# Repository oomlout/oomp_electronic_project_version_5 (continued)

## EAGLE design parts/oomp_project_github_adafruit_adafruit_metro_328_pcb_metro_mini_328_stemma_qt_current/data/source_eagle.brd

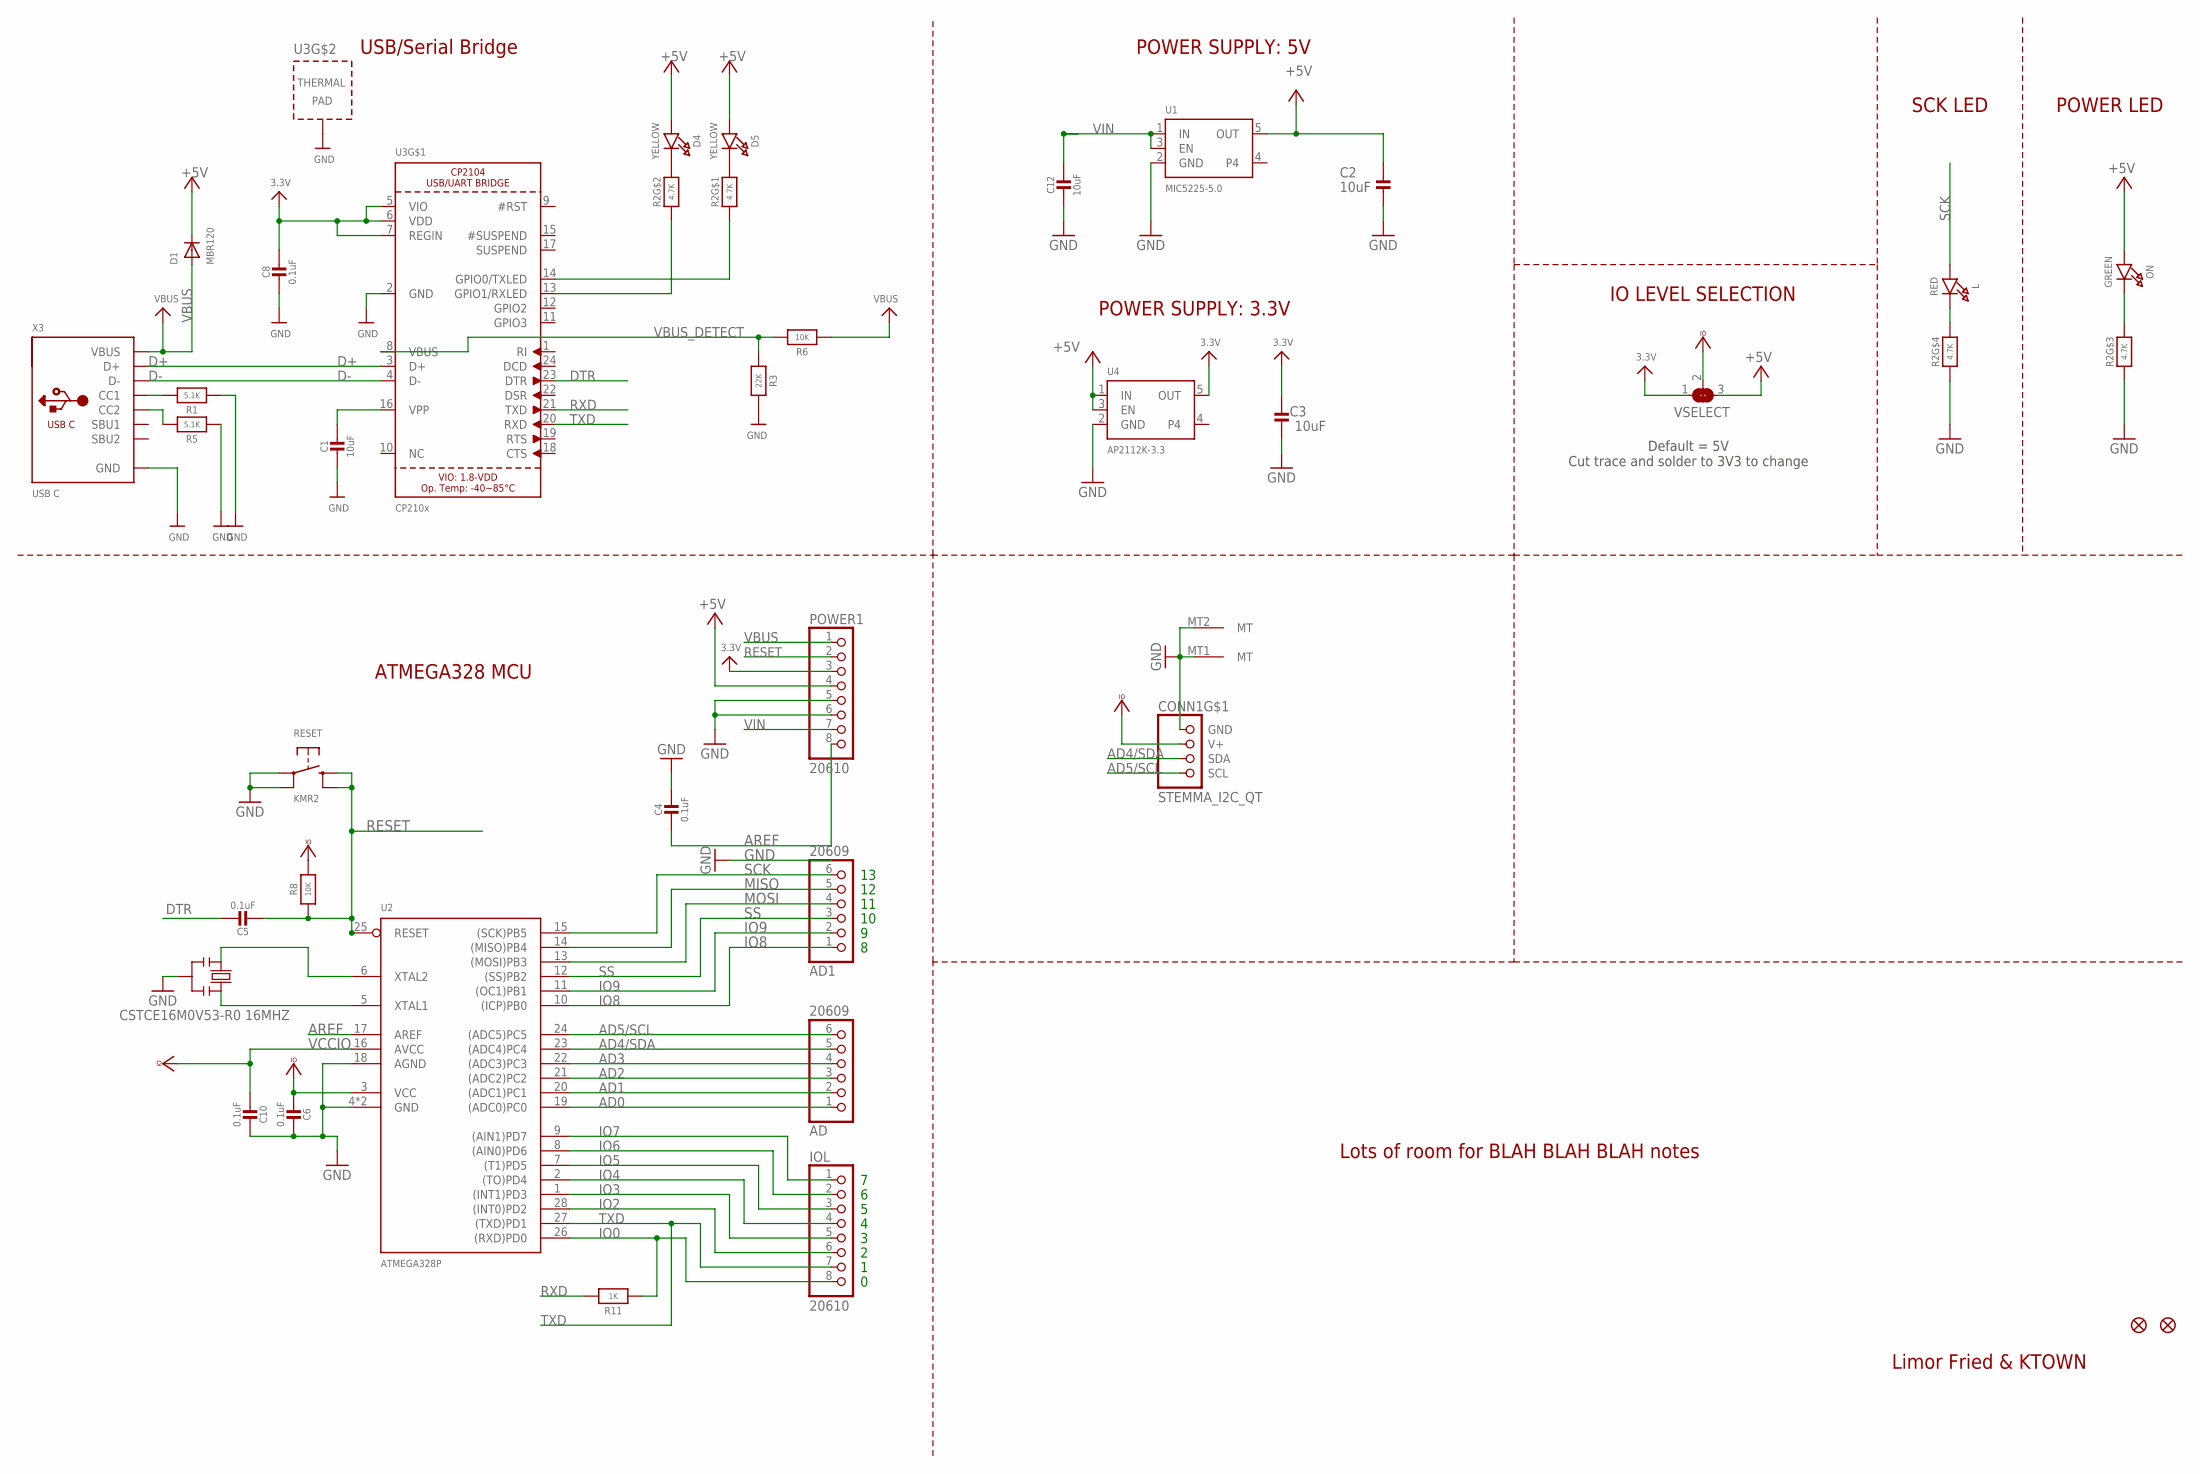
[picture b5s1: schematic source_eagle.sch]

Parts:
AD, AD1: 20609; 1X06_ROUND
C1, C2, C3, C12: 10uF; 0805-NO
C4, C5, C6, C8, C10: 0.1uF; 0603-NO
CONN1: STEMMA_I2C_QT; JST_SH4
D1: MBR120; SOD-123FL
D4, D5: YELLOW; CHIPLED_0603_NOOUTLINE
FD1, FD2: FIDUCIAL_1MM
IOL: 20610; 1X08_ROUND
L: RED; CHIPLED_0603_NOOUTLINE
ON: GREEN; CHIPLED_0603_NOOUTLINE
POWER1: 20610; 1X08_ROUND_70
R1, R5: 5.1K; 0603-NO
R2: 4.7K; RESPACK_4X0603
R3: 22K; 0603-NO
R6, R8: 10K; 0603-NO
R11: 1K; 0603-NO
RESET: KMR2; BTN_KMR2_4.6X2.8
U1: MIC5225-5.0; SOT23-5
U2: ATMEGA328P; QFN28_4MM_.45MM
U3: CP210x; QFN24_4MM_SMSC
U4: AP2112K-3.3; SOT23-5
VSELECT: SOLDERJUMPER_2WAY; SOLDERJUMPER_2WAY_OPEN_NOPASTE
X3: USB C; USB_C_CUSB31-CFM2AX-01-X
Y2: CSTCE16M0V53-R0 16MHZ; RESONATOR

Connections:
3.3V: C3.2, C8.1, POWER1.3, U3.5 (VIO), U3.6 (VDD), U3.7 (REGIN), U4.5 (OUT), VSELECT.1
+5V: C2.2, D1.C, D4.A, D5.A, ON.A, POWER1.4, U1.5 (OUT), U4.1 (IN), U4.3 (EN), VSELECT.3
AD0: AD.1, U2.19 ((ADC0)PC0)
AD1: AD.2, U2.20 ((ADC1)PC1)
AD2: AD.3, U2.21 ((ADC2)PC2)
AD3: AD.4, U2.22 ((ADC3)PC3)
AD4/SDA: AD.5, CONN1.3 (SDA), U2.23 ((ADC4)PC4)
AD5/SCL: AD.6, CONN1.4 (SCL), U2.24 ((ADC5)PC5)
AREF: C4.2, POWER1.8, U2.17 (AREF)
D+: U3.3 (D+), X3.A6 (D+), X3.B6 (D+)
D-: U3.4 (D-), X3.A7 (D-), X3.B7 (D-)
DTR: C5.1, U3.23 (DTR)
GND: C1.2, C2.1, C3.1, C4.1, C6.1, C8.2, C10.1, C12.2, CONN1.1 (GND), CONN1.MT1 (MT), CONN1.MT2 (MT), POWER1.5, POWER1.6, R1.1, R2.3 (1), R2.4 (1), R3.1, R5.1, RESET.A, RESET.A' (P1), U1.2 (GND), U2.4 (GND), U2.18 (AGND), U2.29 (GND), U3.2 (GND), U3.THERM (TP), U4.2 (GND), X3.A1B12 (GND), X3.B1A12 (GND), Y2.2
IO0: IOL.8, R11.1, U2.26 ((RXD)PD0)
IO2: IOL.6, U2.28 ((INT0)PD2)
IO3: IOL.5, U2.1 ((INT1)PD3)
IO4: IOL.4, U2.2 ((TO)PD4)
IO5: IOL.3, U2.7 ((T1)PD5)
IO6: IOL.2, U2.8 ((AIN0)PD6)
IO7: IOL.1, U2.9 ((AIN1)PD7)
IO8: AD1.1, U2.10 ((ICP)PB0)
IO9: AD1.2, U2.11 ((OC1)PB1)
MISO: AD1.5, U2.14 ((MISO)PB4)
MOSI: AD1.4, U2.13 ((MOSI)PB3)
unnamed: L.C, R2.5 (2)
unnamed: ON.C, R2.6 (2)
unnamed: R2.1, U3.14 (GPIO0/TXLED)
unnamed: R1.2, X3.A5 (CC1)
unnamed: D4.C, R2.7 (2)
unnamed: D5.C, R2.8 (2)
unnamed: R5.2, X3.B5 (CC2)
unnamed: C1.1, U3.16 (VPP)
unnamed: R2.2 (1), U3.13 (GPIO1/RXLED)
RESET: C5.2, POWER1.2, R8.1, RESET.B (S), RESET.B' (S1), U2.25 (RESET)
RXD: R11.2, U3.21 (TXD)
SCK: AD1.6, L.A, U2.15 ((SCK)PB5)
SS: AD1.3, U2.12 ((SS)PB2)
TXD: IOL.7, U2.27 ((TXD)PD1), U3.20 (RXD)
VBUS: D1.A, POWER1.1, R6.2, X3.A4B9 (VBUS), X3.B4A9 (VBUS)
VBUS_DETECT: R3.2, R6.1, U3.8 (VBUS)
VCCIO: C6.2, C10.2, CONN1.2 (V+), R8.2, U2.3 (VCC), U2.16 (AVCC), VSELECT.2
VIN: C12.1, POWER1.7, U1.1 (IN), U1.3 (EN)
XTAL1: U2.5 (XTAL1), Y2.3
XTAL2: U2.6 (XTAL2), Y2.1

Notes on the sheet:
Limor Fried & KTOWN
POWER SUPPLY: 5V
USB/Serial Bridge
POWER SUPPLY: 3.3V
IO LEVEL SELECTION
POWER LED
ATMEGA328 MCU
SCK LED
Lots of room for BLAH BLAH BLAH notes
Default = 5V Cut trace and solder to 3V3 to change

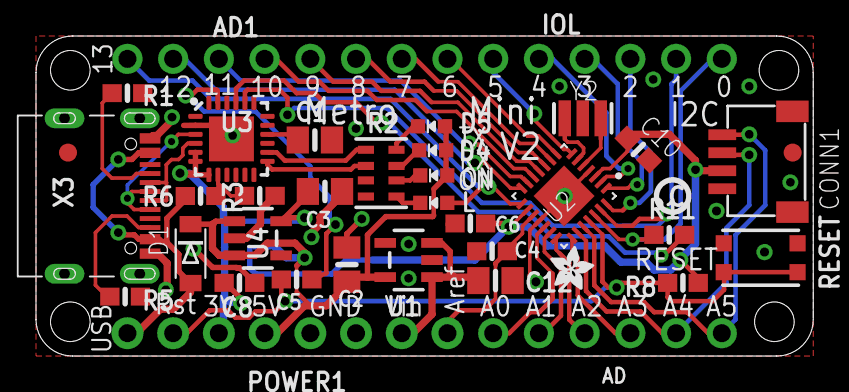
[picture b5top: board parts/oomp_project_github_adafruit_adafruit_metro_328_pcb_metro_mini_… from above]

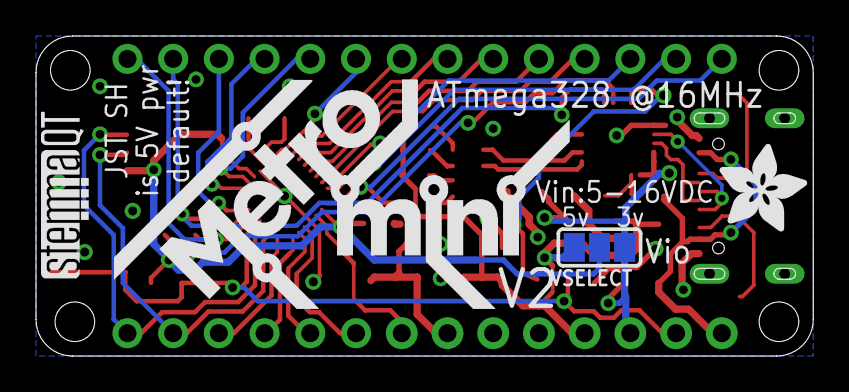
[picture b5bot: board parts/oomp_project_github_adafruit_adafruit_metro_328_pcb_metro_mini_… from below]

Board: 2 copper layers, 43.2 x 17.8 mm, 41 parts (4 on the bottom side), 44 nets.

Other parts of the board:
U$4: PCBFEAT-REV-040
U$5: ADAFRUIT_2.5MM
U$6: STEMMAQT
U$7: METROMINI_SILK
U$10: ADAFRUIT_5MM

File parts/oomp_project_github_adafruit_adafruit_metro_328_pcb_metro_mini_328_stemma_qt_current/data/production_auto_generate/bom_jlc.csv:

Comment,Designator,Footprint,LCSC Part #
,U$5,Metro Mini 328 V2 - STEMMA QT-import-fps:ADAFRUIT_2.5MM,
,U$10,Metro Mini 328 V2 - STEMMA QT-import-fps:ADAFRUIT_5MM,
,U$7,Metro Mini 328 V2 - STEMMA QT-import-fps:METROMINI_SILK,
,U$4,Metro Mini 328 V2 - STEMMA QT-import-fps:PCBFEAT-REV-040,
,VSELECT0,Metro Mini 328 V2 - STEMMA QT-import-fps:SOLDERJUMPER_2WAY_OPEN_NOPASTE,
,U$6,Metro Mini 328 V2 - STEMMA QT-import-fps:STEMMAQT,
0.1uF,"C4,C5,C6,C8,C10",Metro Mini 328 V2 - STEMMA QT-import-fps:0603-NO,C14663
10K,"R6,R8",Metro Mini 328 V2 - STEMMA QT-import-fps:0603-NO,C98220
10uF,"C1,C2,C3,C12",Metro Mini 328 V2 - STEMMA QT-import-fps:0805-NO,
1K,R11,Metro Mini 328 V2 - STEMMA QT-import-fps:0603-NO,C2907002
20609,"AD0,AD1",Metro Mini 328 V2 - STEMMA QT-import-fps:1X06_ROUND,C37208
20610,IOL0,Metro Mini 328 V2 - STEMMA QT-import-fps:1X08_ROUND,C492421
20610,POWER1,Metro Mini 328 V2 - STEMMA QT-import-fps:1X08_ROUND_70,C492421
22K,R3,Metro Mini 328 V2 - STEMMA QT-import-fps:0603-NO,C31850
4.7K,R2,Metro Mini 328 V2 - STEMMA QT-import-fps:RESPACK_4X0603,C23162
5.1K,"R1,R5",Metro Mini 328 V2 - STEMMA QT-import-fps:0603-NO,C23186
AP2112K-3.3,U4,Metro Mini 328 V2 - STEMMA QT-import-fps:SOT23-5,
ATMEGA328P,U2,Metro Mini 328 V2 - STEMMA QT-import-fps:QFN28_4MM_.45MM,
CP210x,U3,Metro Mini 328 V2 - STEMMA QT-import-fps:QFN24_4MM_SMSC,
CSTCE16M0V53-R0 16MHZ,Y2,Metro Mini 328 V2 - STEMMA QT-import-fps:RESONATOR,
FIDUCIAL_1MM,"FD1,FD2",Metro Mini 328 V2 - STEMMA QT-import-fps:FIDUCIAL_1MM,
GREEN,ON0,Metro Mini 328 V2 - STEMMA QT-import-fps:CHIPLED_0603_NOOUTLINE,
KMR2,RESET0,Metro Mini 328 V2 - STEMMA QT-import-fps:BTN_KMR2_4.6X2.8,
MBR120,D1,Metro Mini 328 V2 - STEMMA QT-import-fps:SOD-123FL,
MIC5225-5.0,U1,Metro Mini 328 V2 - STEMMA QT-import-fps:SOT23-5,
RED,L0,Metro Mini 328 V2 - STEMMA QT-import-fps:CHIPLED_0603_NOOUTLINE,
STEMMA_I2C_QT,CONN1,Metro Mini 328 V2 - STEMMA QT-import-fps:JST_SH4,C160404
USB C,X3,Metro Mini 328 V2 - STEMMA QT-import-fps:USB_C_CUSB31-CFM2AX-01-X,
YELLOW,"D4,D5",Metro Mini 328 V2 - STEMMA QT-import-fps:CHIPLED_0603_NOOUTLINE,

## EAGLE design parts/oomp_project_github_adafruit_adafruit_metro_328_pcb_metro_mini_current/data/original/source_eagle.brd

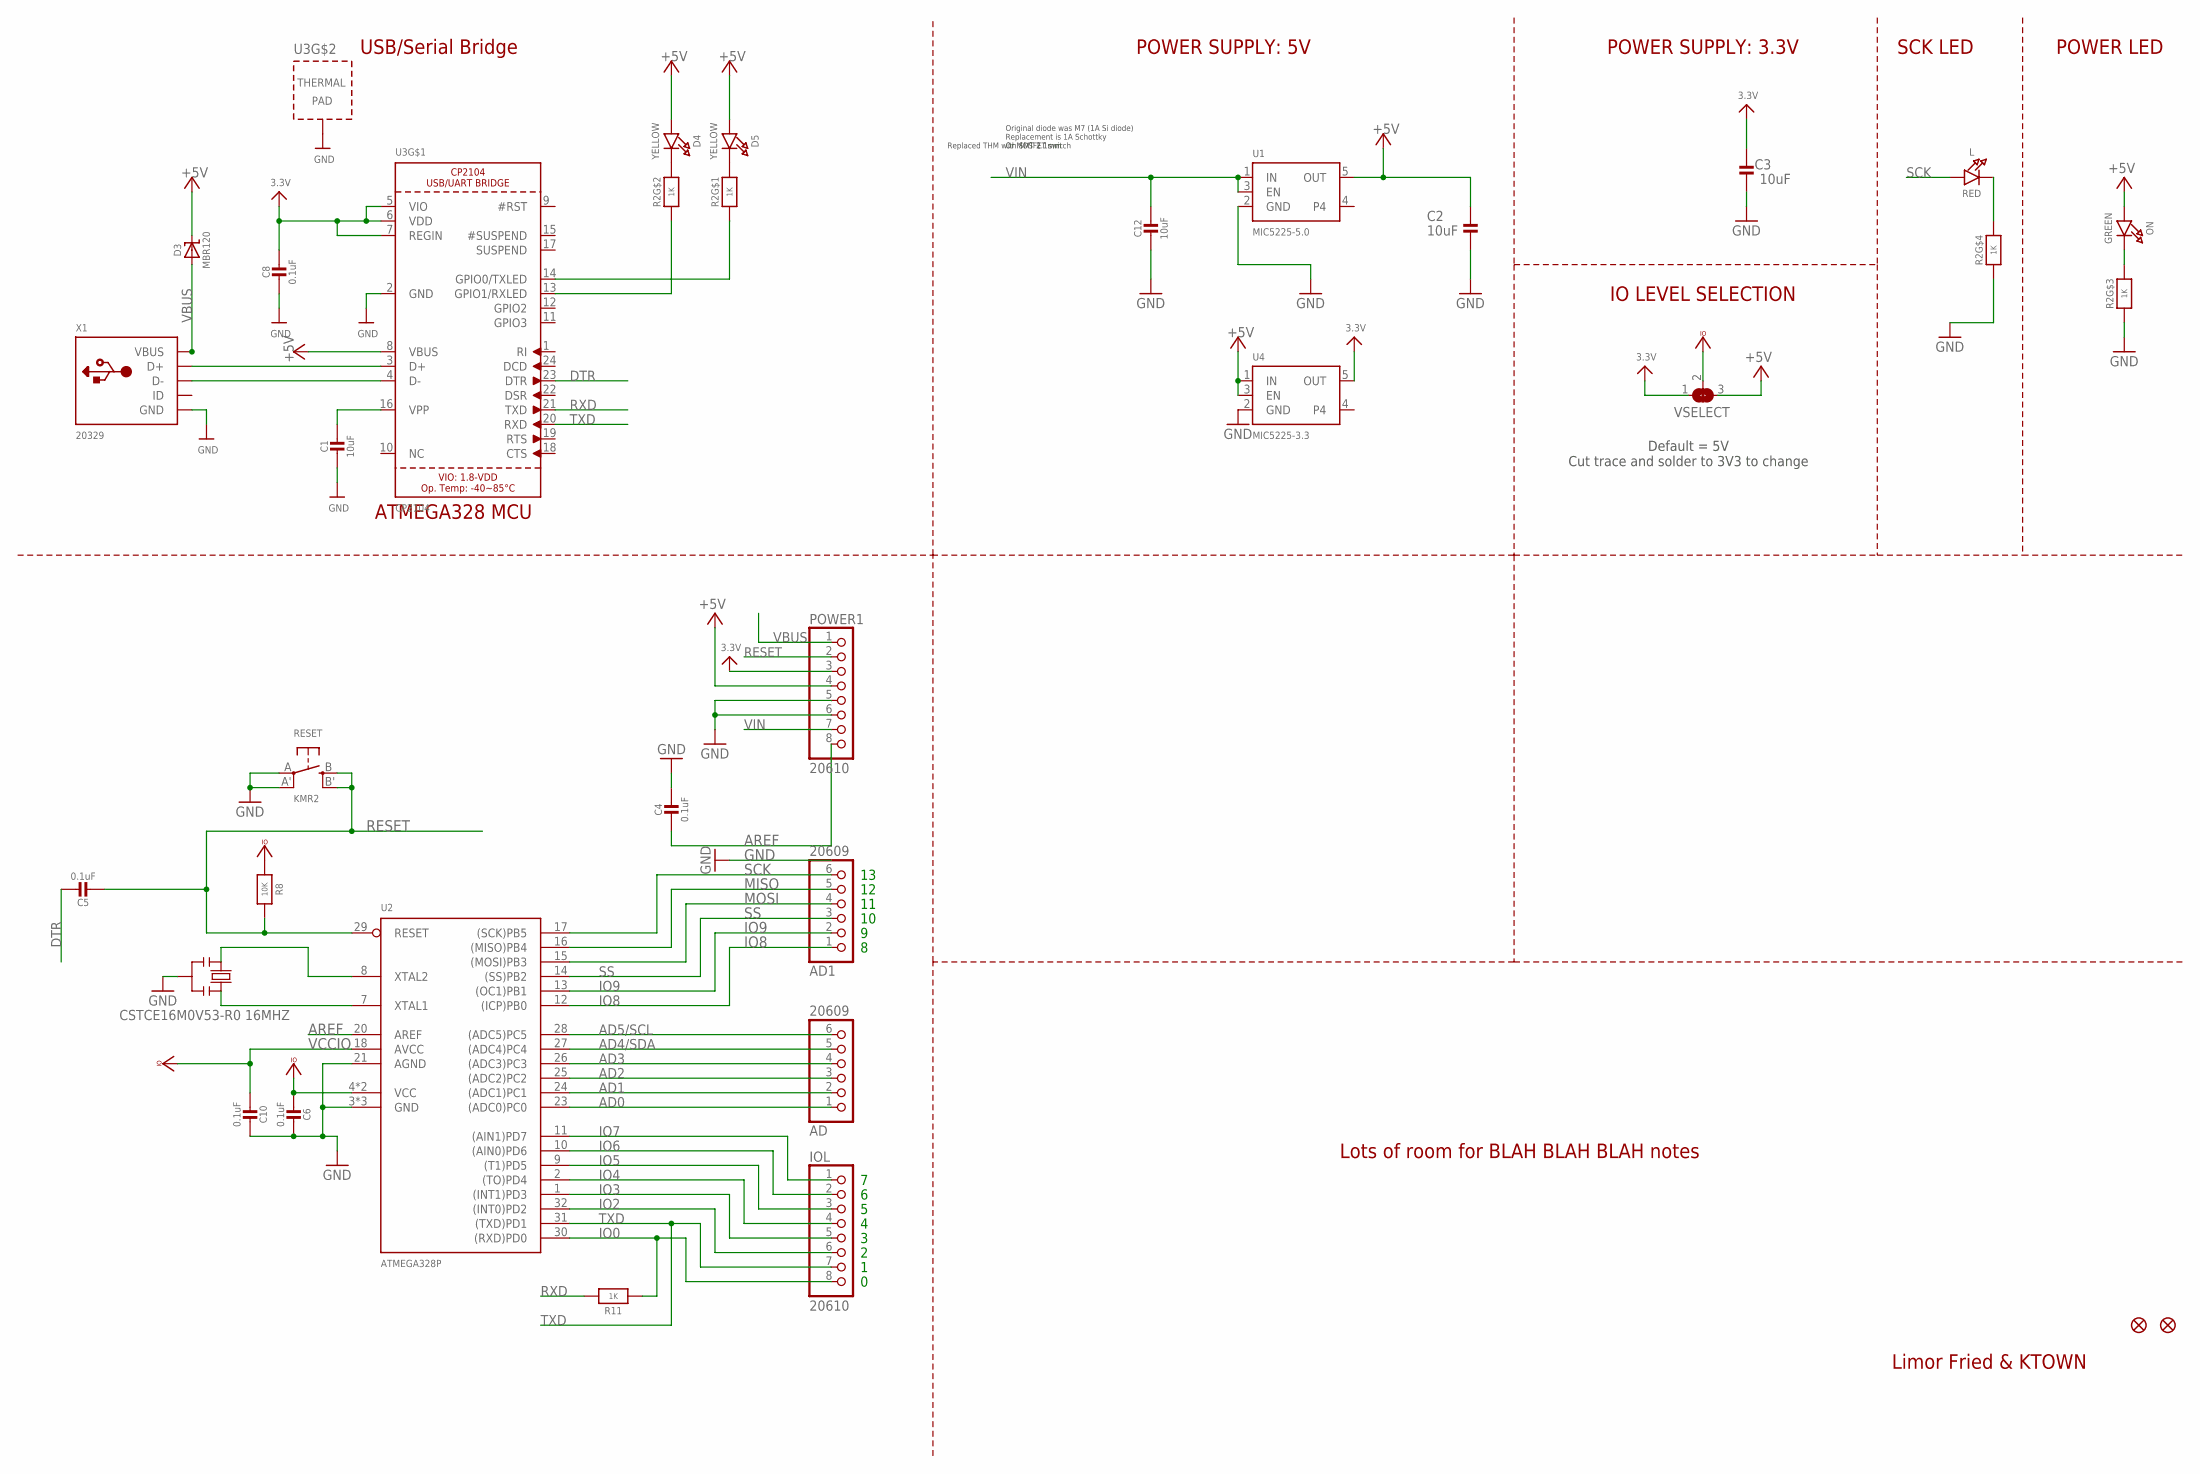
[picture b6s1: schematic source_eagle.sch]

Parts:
AD, AD1: 20609; 1X06_ROUND
C1, C2, C3, C12: 10uF; 0805-NO
C4, C6, C8, C10: 0.1uF; 0805-NO
C5: 0.1uF; _0805MP
D3: MBR120; SOD-123
D4, D5: YELLOW; CHIPLED_0805_NOOUTLINE
FD1, FD2: FIDUCIAL""; FIDUCIAL_1MM
IOL: 20610; 1X08_ROUND
L: RED; CHIPLED_0805_NOOUTLINE
ON: GREEN; CHIPLED_0805_NOOUTLINE
POWER1: 20610; 1X08_ROUND_70
R2: 1K; RESPACK_4X0603
R8: 10K; 0805-NO
R11: 1K; 0805-NO
RESET: KMR2; BTN_KMR2_4.6X2.8
U1: MIC5225-5.0; SOT23-5
U2: ATMEGA328P; MLF32-TH
U3: CP2104; QFN24_4MM_SMSC
U4: MIC5225-3.3; SOT23-5
VSELECT: SOLDERJUMPER_2WAY; SOLDERJUMPER_2WAY_OPEN_NOPASTE
X1: 20329; 4UCONN_20329_V2
Y2: CSTCE16M0V53-R0 16MHZ; RESONATOR

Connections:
3.3V: C3.2, C8.1, POWER1.3, U3.5 (VIO), U3.6 (VDD), U3.7 (REGIN), U4.5 (OUT), VSELECT.1
+5V: C2.2, D3.C, D4.A, D5.A, ON.A, POWER1.4, U1.5 (OUT), U3.8 (VBUS), U4.1 (IN), U4.3 (EN), VSELECT.3
AD0: AD.1, U2.23 ((ADC0)PC0)
AD1: AD.2, U2.24 ((ADC1)PC1)
AD2: AD.3, U2.25 ((ADC2)PC2)
AD3: AD.4, U2.26 ((ADC3)PC3)
AD4/SDA: AD.5, U2.27 ((ADC4)PC4)
AD5/SCL: AD.6, U2.28 ((ADC5)PC5)
AREF: C4.2, POWER1.8, U2.20 (AREF)
DTR: C5.1, U3.23 (DTR)
GND: C1.2, C2.1, C3.1, C4.1, C6.1, C8.2, C10.1, C12.2, POWER1.5, POWER1.6, R2.3 (1), R2.4 (1), RESET.A, RESET.A' (P1), U1.2 (GND), U2.3 (GND), U2.5 (GND), U2.21 (AGND), U2.TH (GND), U3.2 (GND), U3.THERM (TP), U4.2 (GND), X1.BASE@1 (GND), X1.BASE@2 (GND), X1.GND, X1.SPRT@1 (GND), X1.SPRT@2 (GND), X1.SPRT@3 (GND), X1.SPRT@4 (GND), Y2.2
IO0: IOL.8, R11.1, U2.30 ((RXD)PD0)
IO2: IOL.6, U2.32 ((INT0)PD2)
IO3: IOL.5, U2.1 ((INT1)PD3)
IO4: IOL.4, U2.2 ((TO)PD4)
IO5: IOL.3, U2.9 ((T1)PD5)
IO6: IOL.2, U2.10 ((AIN0)PD6)
IO7: IOL.1, U2.11 ((AIN1)PD7)
IO8: AD1.1, U2.12 ((ICP)PB0)
IO9: AD1.2, U2.13 ((OC1)PB1)
MISO: AD1.5, U2.16 ((MISO)PB4)
MOSI: AD1.4, U2.15 ((MOSI)PB3)
unnamed: L.C, R2.5 (2)
unnamed: ON.C, R2.6 (2)
unnamed: R2.1, U3.14 (GPIO0/TXLED)
unnamed: D4.C, R2.7 (2)
unnamed: D5.C, R2.8 (2)
unnamed: U3.3 (D+), X1.D+
unnamed: U3.4 (D-), X1.D-
unnamed: C1.1, U3.16 (VPP)
unnamed: R2.2 (1), U3.13 (GPIO1/RXLED)
RESET: C5.2, POWER1.2, R8.1, RESET.B (S), RESET.B' (S1), U2.29 (RESET)
RXD: R11.2, U3.21 (TXD)
SCK: AD1.6, L.A, U2.17 ((SCK)PB5)
SS: AD1.3, U2.14 ((SS)PB2)
TXD: IOL.7, U2.31 ((TXD)PD1), U3.20 (RXD)
VBUS: D3.A, POWER1.1, X1.VBUS
VCCIO: C6.2, C10.2, R8.2, U2.4 (VCC), U2.6 (VCC), U2.18 (AVCC), VSELECT.2
VIN: C12.1, POWER1.7, U1.1 (IN), U1.3 (EN)
XTAL1: U2.7 (XTAL1), Y2.3
XTAL2: U2.8 (XTAL2), Y2.1

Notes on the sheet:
Limor Fried & KTOWN
Original diode was M7 (1A Si diode) Replacement is 1A Schottky Or MOSFET switch
Replaced THM with SMT 2.1mm
POWER SUPPLY: 5V
USB/Serial Bridge
POWER SUPPLY: 3.3V
IO LEVEL SELECTION
POWER LED
ATMEGA328 MCU
SCK LED
Lots of room for BLAH BLAH BLAH notes
Default = 5V Cut trace and solder to 3V3 to change

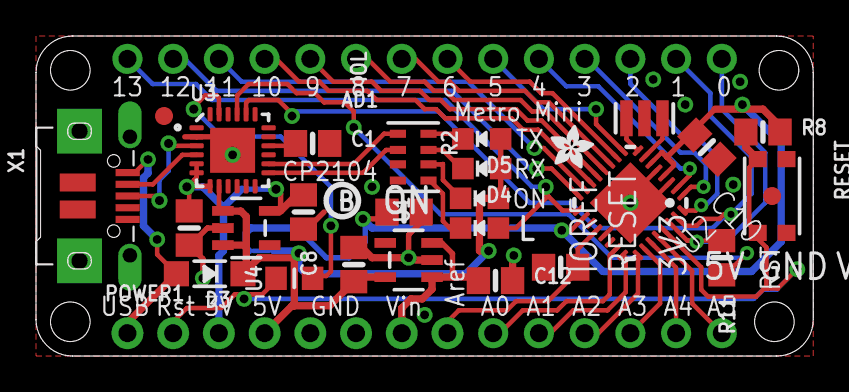
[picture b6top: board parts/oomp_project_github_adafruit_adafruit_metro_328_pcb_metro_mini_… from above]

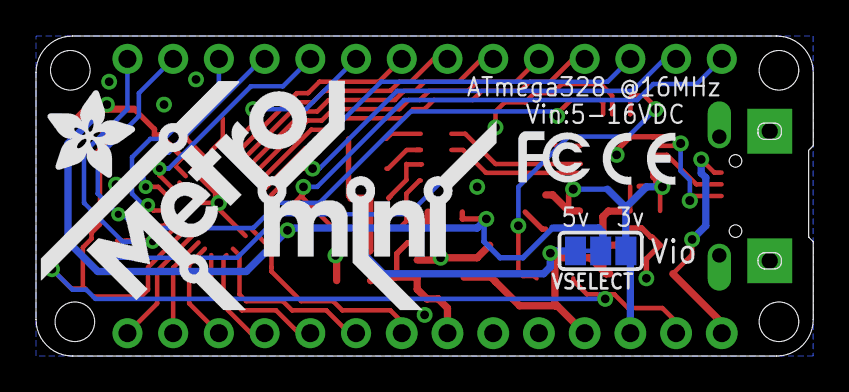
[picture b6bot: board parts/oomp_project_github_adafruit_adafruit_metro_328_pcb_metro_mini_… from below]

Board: 2 copper layers, 43.2 x 17.8 mm, 37 parts (5 on the bottom side), 41 nets.

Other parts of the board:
U$4: PCBFEAT-REV-040
U$5: ADAFRUIT_2.5MM
U$7: METROMINI_SILK
U$10: ADAFRUIT_5MM
U$12: SYMBOL_CE_TINY
U$14: SYMBOL_FCC_TINY

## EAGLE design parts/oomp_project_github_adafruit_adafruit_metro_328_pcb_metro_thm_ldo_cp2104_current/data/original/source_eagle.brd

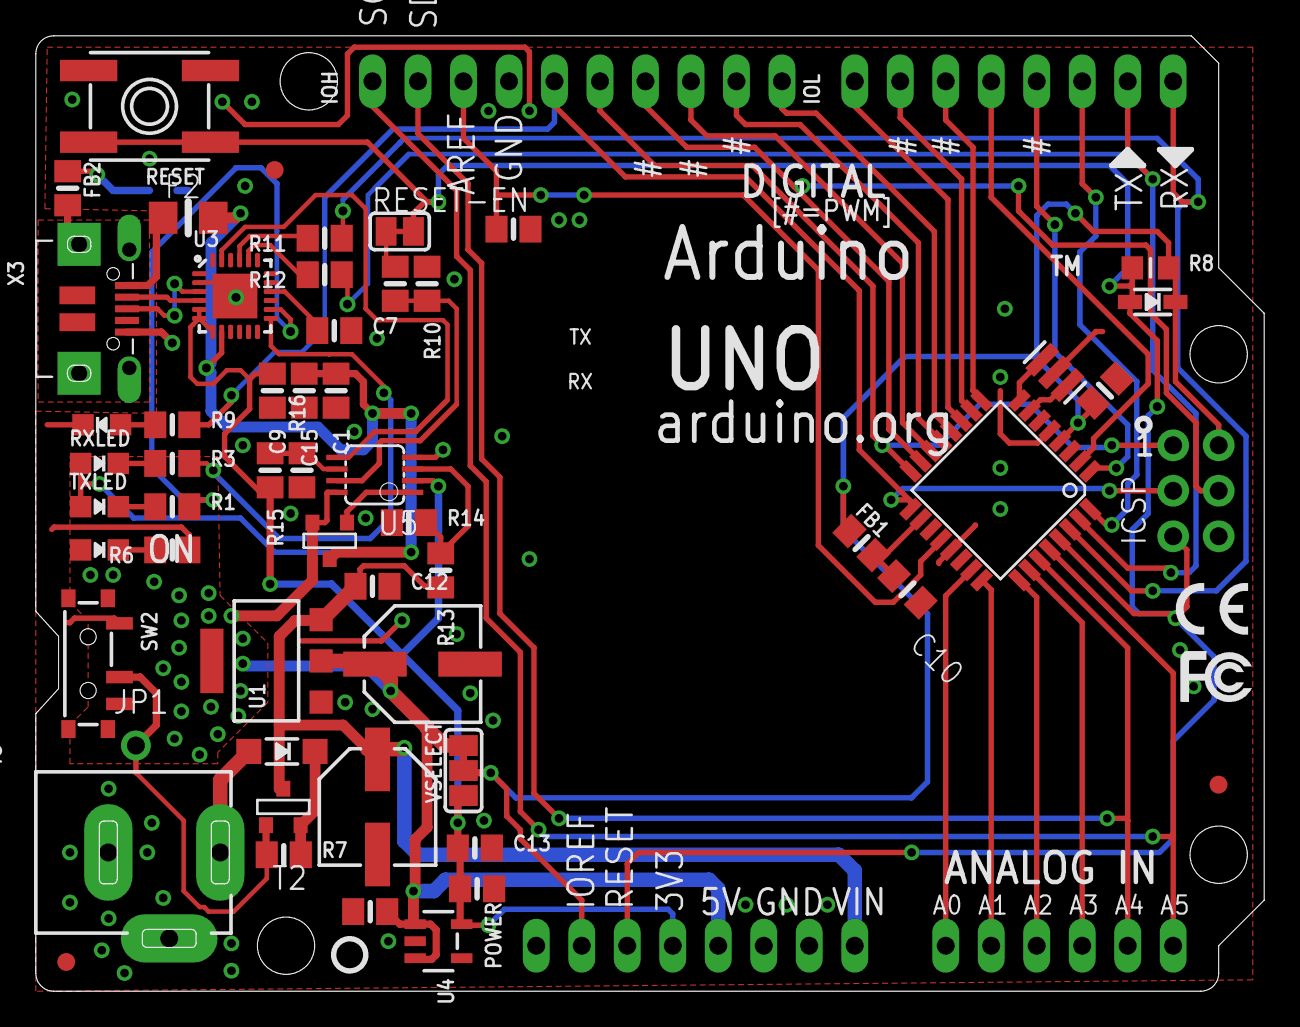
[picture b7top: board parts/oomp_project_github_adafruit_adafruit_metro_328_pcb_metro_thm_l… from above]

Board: 2 copper layers, 68.6 x 53.3 mm, 65 parts (1 on the bottom side), 53 nets.

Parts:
AD: 20609; 1X06_OVAL
C1, C3, C7: 10uF; 0805-NO
C2, C4, C5, C6, C9, C12, C13, C15: 0.1uF; 0805-NO
C10: 0.1uF; 0805_10MGAP
D1: MBR120; SOD-123
D2: 1N4148; SOD-323
F2: 500mA; 1206-NO
FB1, FB2: FERRITE; 0805-NO
FD1, FD2, FD3: FIDUCIAL_1MM
GROUND1: SJ
ICSP: 3x2 M; 2X03_ROUND_70MIL
IOH: 20611; 1X10_OVAL
IOL: 20610; 1X08_OVAL
JP1: 1X01_ROUND
L: RED; CHIPLED_0805_NOOUTLINE
ON: GREEN; CHIPLED_0805_NOOUTLINE
PC1: 47uF/25V; PANASONIC_D
PC2: 47uF+/6.3V+; PANASONIC_D
POWER: 20610; 1X08_OVAL
R1, R3, R6, R9, R10, R11, R12: 1K; 0805-NO
R7, R13, R14, R15, R16: 10K; 0805-NO
R8: 10K; _0805MP
RESET: 6mm; EVQ-Q2
RESET-EN: SOLDERJUMPER_CLOSEDWIRE
RXLED: YELLOW; CHIPLED_0805_NOOUTLINE
SW2: SPDT_SMT_SSSS811101
T1, T2: DMP3098L; SOT-23
TXLED: YELLOW; CHIPLED_0805_NOOUTLINE
U1: NCP1117ST50T3G; SOT223-R
U3: CP2104; QFN24_4MM_SMSC
U4: AP2112-3.3; SOT23-5
U5: LMV358IDGKR; MSOP08
U$4: METROSILK_CP2104_TOP
U$14: METROSILK_BOT
U$15: PCBFEAT-REV-040
U$16: SYMBOL_FCC_TINY
U$17: SYMBOL_CE_TINY
VSELECT: SOLDERJUMPER_2WAY_OPEN_NOPASTE
X2: DCJACK_2MM_PTH
X3: 20329; 4UCONN_20329_V2
Y2: CSTCE16M0V53-R0 16MHZ; RESONATOR
ZU4: ATMEGA328P-AU; TQFP32-08

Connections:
3.3V: C3.2, C9.1, C13.1, POWER.4, R15.2, U3.5, U3.6, U3.7, U4.5, U5.2, VSELECT.1
+5V: C2.2, ON.A, PC2.+, POWER.5, T1.2, U1.2, U1.4, U4.1, U4.3, U5.8, VSELECT.3
AD0: AD.1, ZU4.23
AD1: AD.2, ZU4.24
AD2: AD.3, ZU4.25
AD3: AD.4, ZU4.26
AD4/SDA: AD.5, IOH.2, ZU4.27
AD5/SCL: AD.6, IOH.1, ZU4.28
AREF: C4.2, IOH.3, ZU4.20
AVCC: C10.2, FB1.2, ZU4.18
CMP: R13.1, R14.2, U5.3
D+: U3.3, X3.D+
D-: U3.4, X3.D-
DTR: U3.23, U5.5
DTR_5V: C5.1, R10.2, U5.7
GATE_CMD: T1.3, U5.1
GND: C1.2, C2.1, C3.1, C4.1, C6.1, C7.2, C9.2, C10.1, C12.2, C13.2, C15.2, GROUND1.2, ICSP.6, IOH.4, L.C, PC1.-, PC2.-, POWER.6, POWER.7, R6.1, R10.1, R14.1, R16.1, RESET.A, RESET.A', SW2.A, U1.1, U3.2, U3.THERM, U4.2, U5.4, X2.GND, X2.GNDBREAK, X3.GND, Y2.2, ZU4.5, ZU4.21
IO0: IOL.8, R11.1, ZU4.30
IO1: IOL.7, R12.1, ZU4.31
IO2: IOL.6, ZU4.32
IO3: IOL.5, ZU4.1
IO4: IOL.4, ZU4.2
IO5: IOL.3, ZU4.9
IO6: IOL.2, ZU4.10
IO7: IOL.1, ZU4.11
IO8: IOH.10, ZU4.12
IO9: IOH.9, ZU4.13
MISO: ICSP.1, IOH.6, ZU4.16
MOSI: ICSP.4, IOH.7, ZU4.15
unnamed: L.A, R9.1
unnamed: FB2.1, GROUND1.1
unnamed: ON.C, R6.2
unnamed: R3.1, RXLED.C
unnamed: R1.1, TXLED.C
unnamed: R15.1, R16.2, U5.6
unnamed: JP1.1, R7.1, SW2.B, T2.3
unnamed: D1.C, R7.2, T2.2
unnamed: C7.1, U3.16
PWRIN: D1.A, X2.PWR
RESET: C5.2, D2.A, ICSP.5, POWER.3, R8.1, RESET.B, RESET.B', RESET-EN.1, RESET-EN.2, ZU4.29
RXD: R11.2, U3.21
RXLED: R3.2, U3.13
SCK: ICSP.3, IOH.5, R9.2, ZU4.17
SS: IOH.8, ZU4.14
TXD: R12.2, U3.20
TXLED: R1.2, U3.14
USBVCC: C1.1, C15.1, F2.2, RXLED.A, T1.1, TXLED.A, U3.8
USHIELD: FB2.2, X3.BASE@1, X3.BASE@2, X3.SPRT@1, X3.SPRT@2, X3.SPRT@3, X3.SPRT@4
VBUS: F2.1, X3.VBUS
VCCIO: C6.2, D2.C, FB1.1, ICSP.2, POWER.2, R8.2, VSELECT.2, ZU4.4
VIN: C12.1, PC1.+, POWER.8, R13.2, T2.1, U1.3
XTAL1: Y2.3, ZU4.7
XTAL2: Y2.1, ZU4.8
